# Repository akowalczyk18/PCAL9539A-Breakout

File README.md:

# PCAL9539A Breakout Board

#### Breakout for using PCAL9539A I2C GPIO expander

Features:
*Nice bright RGB LED for testing
*0.1 headers are breadboard compatible
*Address select jumpers
*Pull-up select jumpers

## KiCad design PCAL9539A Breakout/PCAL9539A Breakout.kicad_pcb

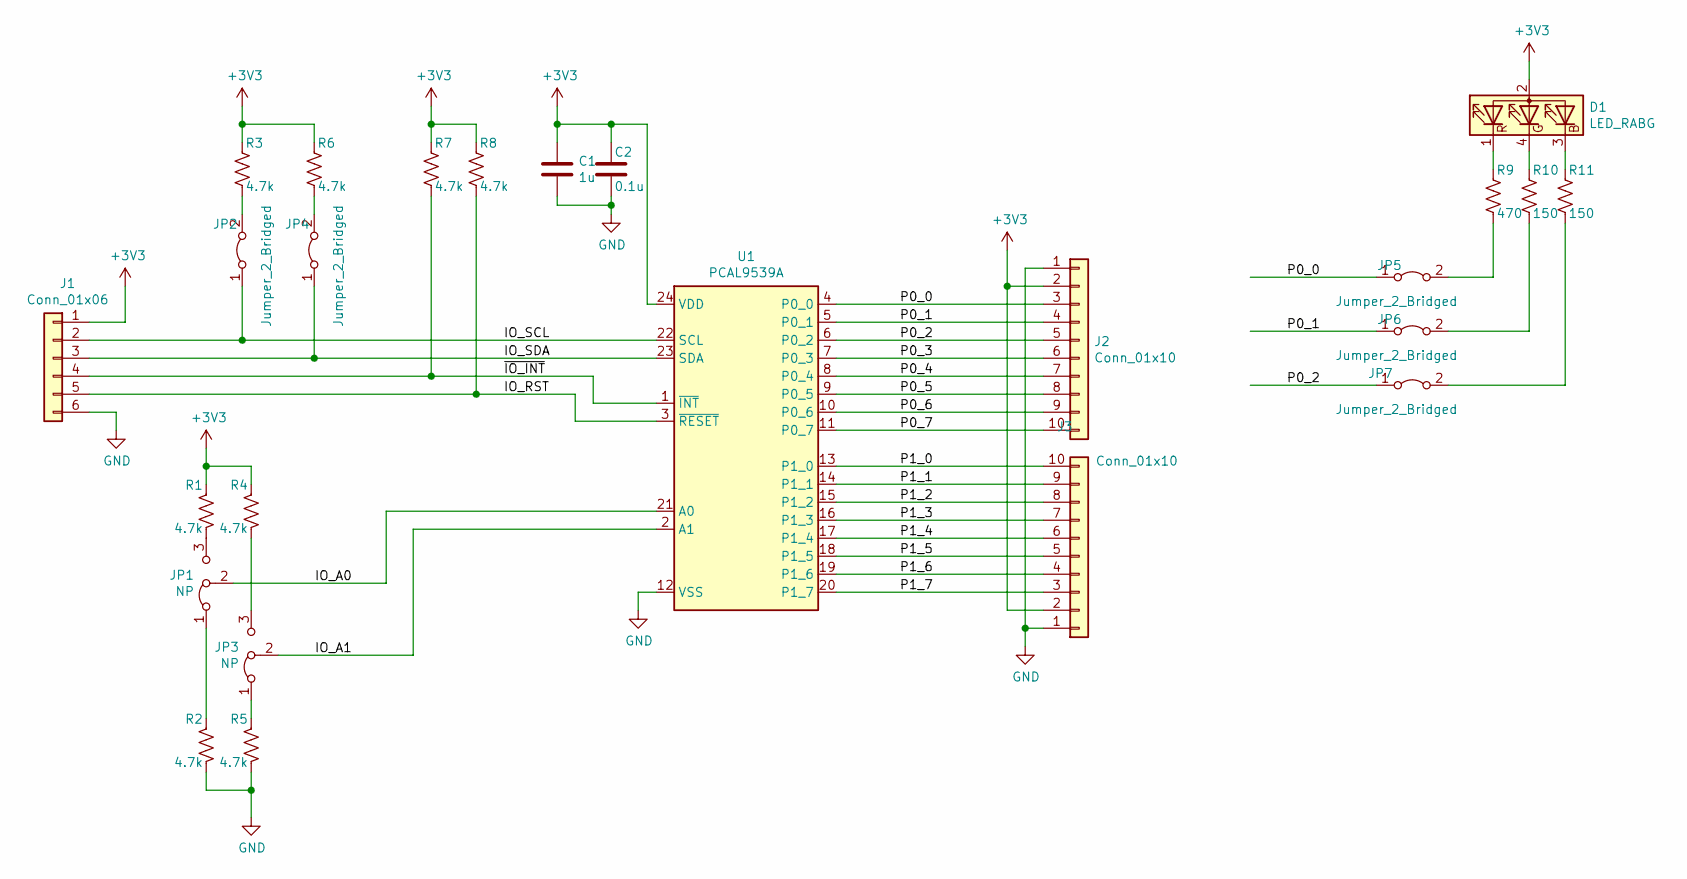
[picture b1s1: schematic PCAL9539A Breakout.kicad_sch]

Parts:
C1: 1u; C_0603_1608Metric
C2: 0.1u; C_0603_1608Metric
D1: LED_RABG; LED_Kingbright_AAA3528ESGCT
J1: Conn_01x06; PinHeader_1x06_P2.54mm_Vertical
J2, J3: Conn_01x10; PinHeader_1x10_P2.54mm_Vertical
JP1, JP3: NP; PinHeader_1x03_P2.54mm_Vertical
JP2, JP4, JP5, JP6, JP7: Jumper_2_Bridged; PinHeader_1x02_P2.54mm_Vertical
R1, R2, R3, R4, R5, R6, R7, R8: 4.7k; R_0603_1608Metric
R9: 470; R_0603_1608Metric
R10, R11: 150; R_0603_1608Metric
U1: PCAL9539A; TSSOP-24_4.4x7.8mm_P0.65mm

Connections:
+3V3: C1.1, C2.1, D1.2 (A), J1.1, J2.2, J3.2, R1.1, R3.1, R4.1, R6.1, R7.1, R8.1, U1.24 (VDD)
/IO_A0: JP1.2 (C), U1.21 (A0)
/IO_A1: JP3.2 (C), U1.2 (A1)
/IO_RST: J1.5, R8.2, U1.3 (~RESET)
/IO_SCL: J1.2, JP2.1 (A), U1.22 (SCL)
/IO_SDA: J1.3, JP4.1 (A), U1.23 (SDA)
/P0_0: J2.3, JP5.1 (A), U1.4 (P0_0)
/P0_1: J2.4, JP6.1 (A), U1.5 (P0_1)
/P0_2: J2.5, JP7.1 (A), U1.6 (P0_2)
/P0_3: J2.6, U1.7 (P0_3)
/P0_4: J2.7, U1.8 (P0_4)
/P0_5: J2.8, U1.9 (P0_5)
/P0_6: J2.9, U1.10 (P0_6)
/P0_7: J2.10, U1.11 (P0_7)
/P1_0: J3.10, U1.13 (P1_0)
/P1_1: J3.9, U1.14 (P1_1)
/P1_2: J3.8, U1.15 (P1_2)
/P1_3: J3.7, U1.16 (P1_3)
/P1_4: J3.6, U1.17 (P1_4)
/P1_5: J3.5, U1.18 (P1_5)
/P1_6: J3.4, U1.19 (P1_6)
/P1_7: J3.3, U1.20 (P1_7)
/~IO_INT: J1.4, R7.2, U1.1 (~INT)
GND: C1.2, C2.2, J1.6, J2.1, J3.1, R2.2, R5.2, U1.12 (VSS)
unnamed: D1.1 (RK), R9.1
unnamed: D1.3 (BK), R11.1
unnamed: D1.4 (GK), R10.1
unnamed: JP1.1 (A), R2.1
unnamed: JP1.3 (B), R1.2
unnamed: JP2.2 (B), R3.2
unnamed: JP3.1 (A), R5.1
unnamed: JP3.3 (B), R4.2
unnamed: JP4.2 (B), R6.2
unnamed: JP5.2 (B), R9.2
unnamed: JP6.2 (B), R10.2
unnamed: JP7.2 (B), R11.2

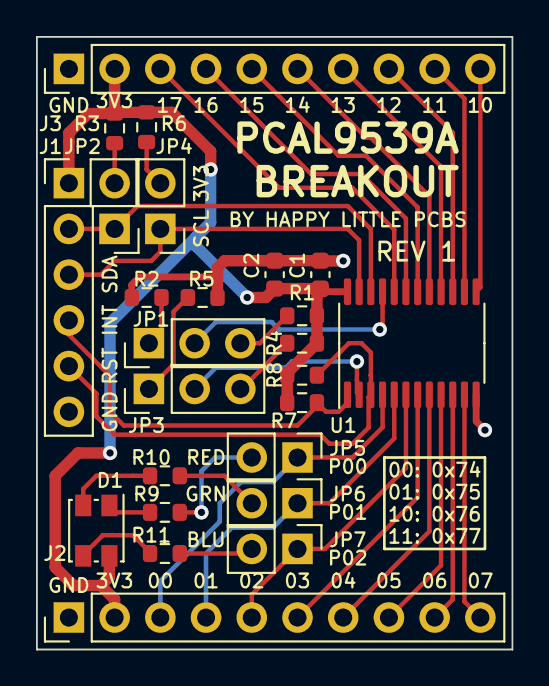
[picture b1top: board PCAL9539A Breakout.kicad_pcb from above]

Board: 2 copper layers, 26.4 x 34.0 mm, 25 parts (0 on the bottom side), 36 nets.

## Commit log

2021-01-30 schematic, copper
2021-01-30 Finished cleanup, silk
2021-02-07 Added gerber files
2021-02-07 added gerbers
2021-08-02 added pictures
